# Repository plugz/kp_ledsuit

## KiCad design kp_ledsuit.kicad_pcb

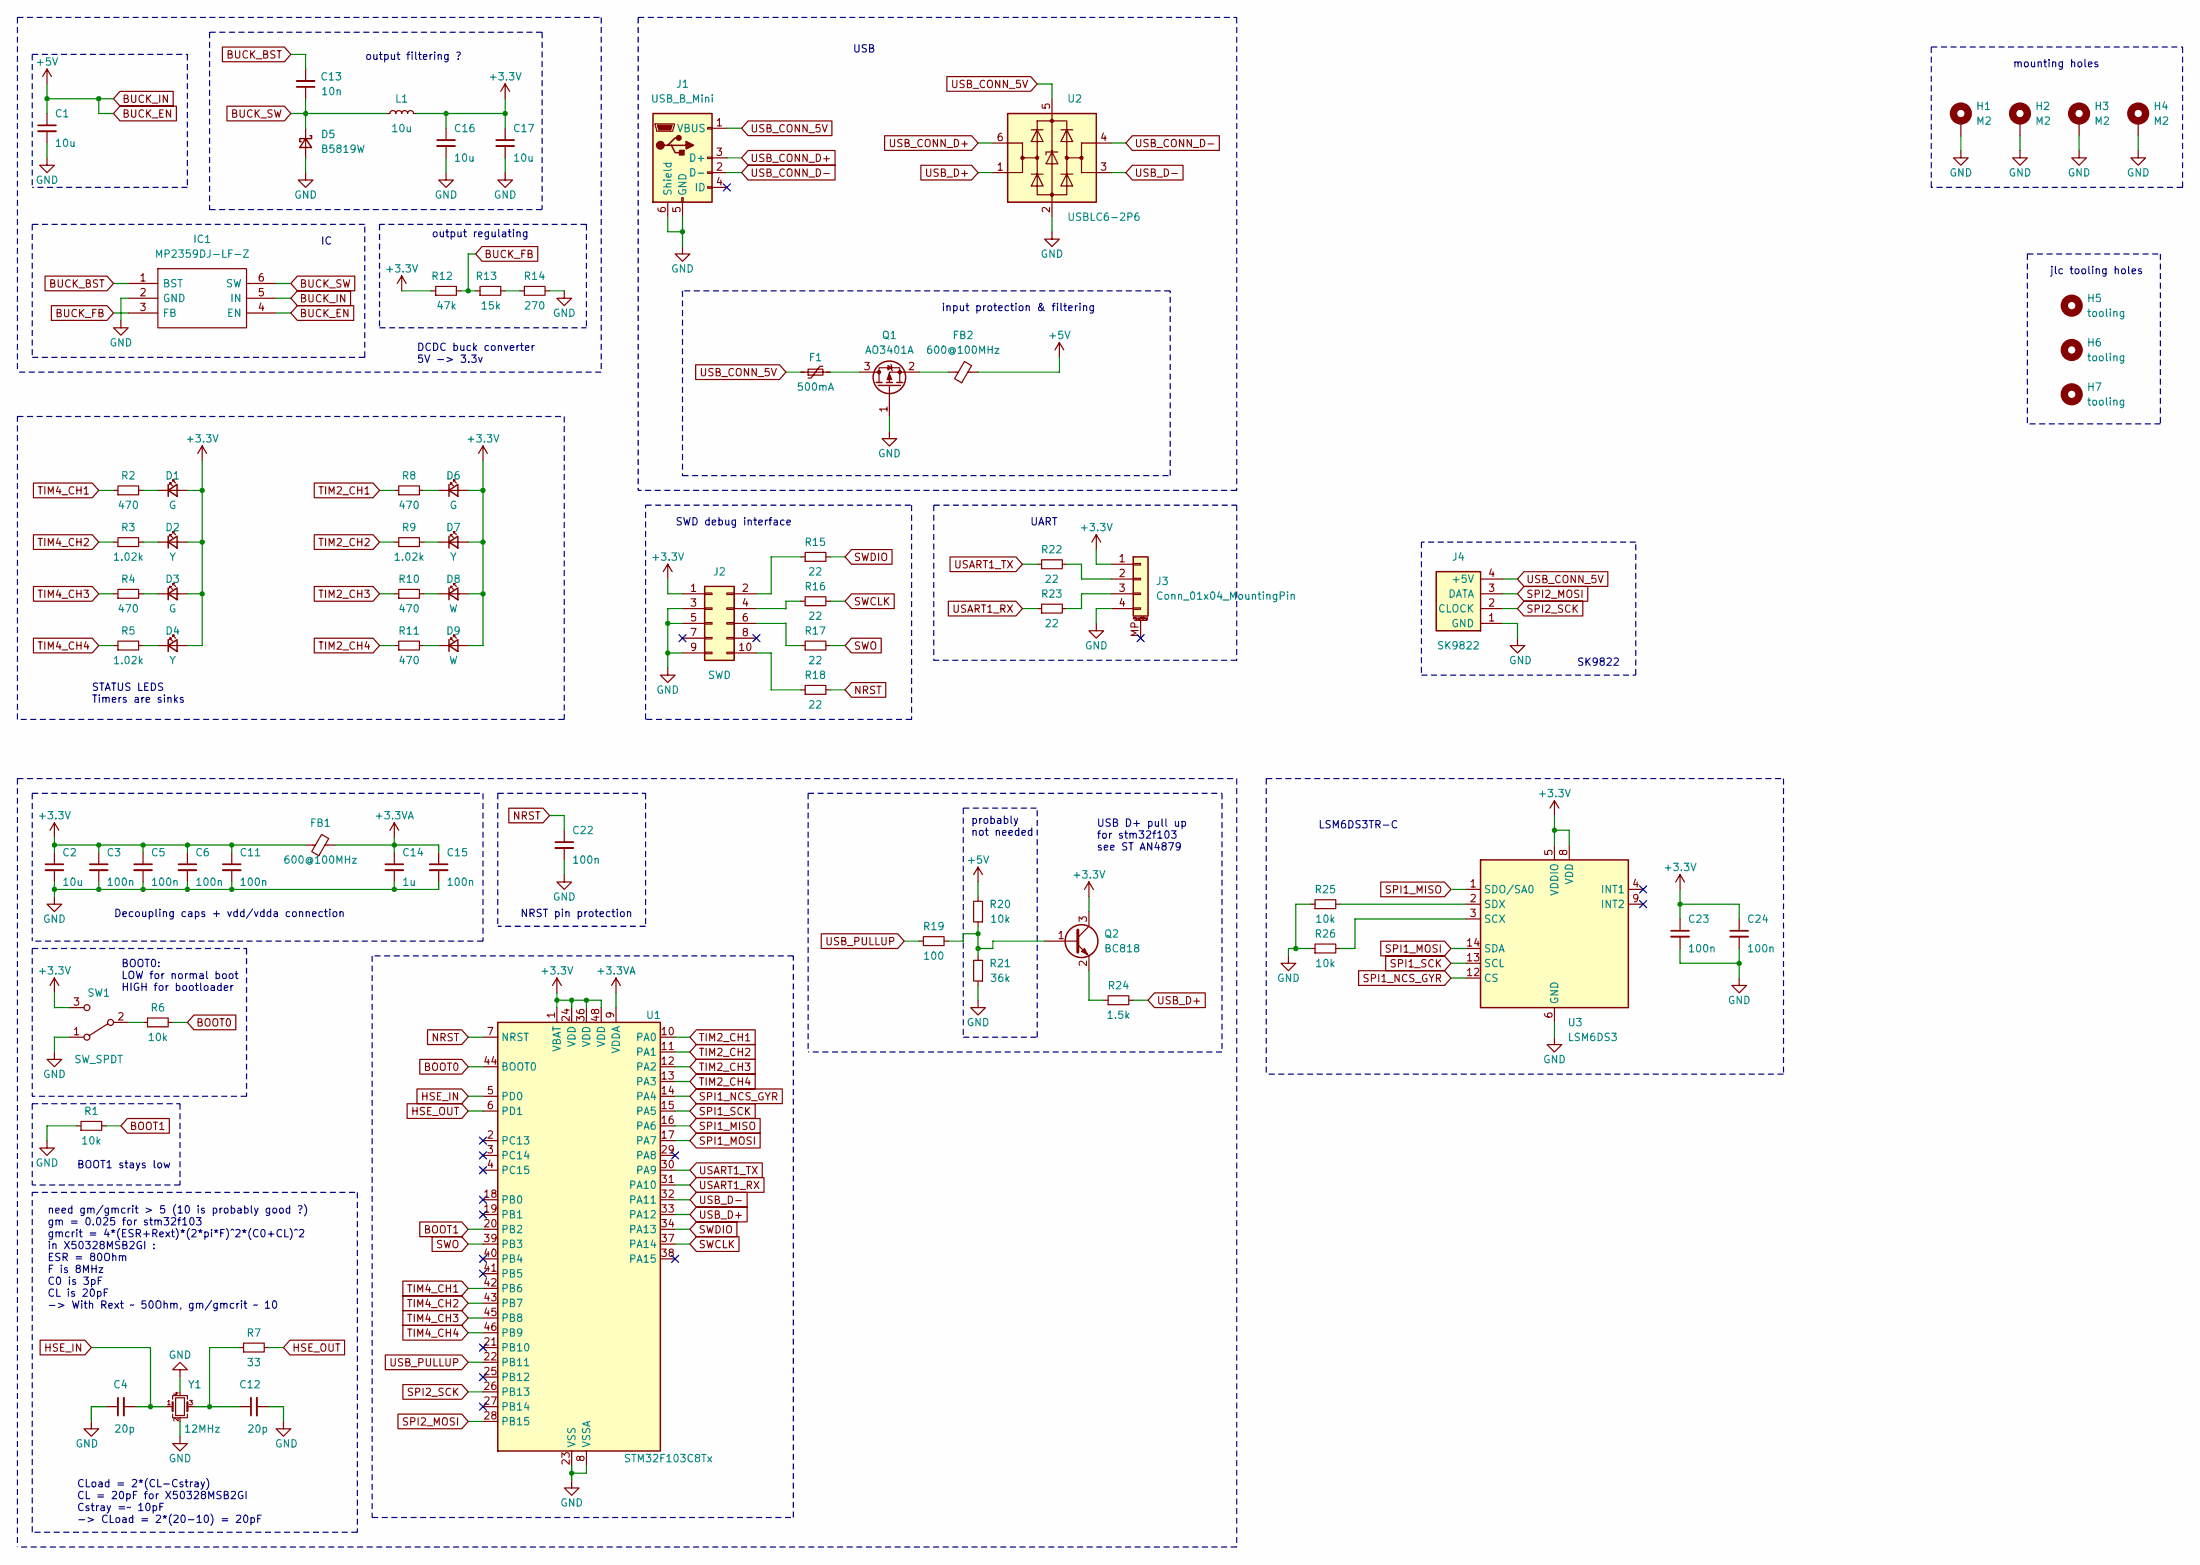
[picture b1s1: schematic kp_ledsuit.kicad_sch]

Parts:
C1, C2, C16, C17: 10u; C_1206_3216Metric; JLCPCB Part # C13585
C3, C5, C6, C11, C15, C22, C23, C24: 100n; C_0402_1005Metric; JLCPCB Part # C307331
C4, C12: 20p; C_0402_1005Metric; JLCPCB Part # C1554
C13: 10n; C_0603_1608Metric; JLCPCB Part # C57112
C14: 1u; C_0805_2012Metric; JLCPCB Part # C28323
D1, D3, D6: G; LED_0805_2012Metric; JLCPCB Part # C2297
D2, D4, D7: Y; LED_0805_2012Metric; JLCPCB Part # C2296
D5: B5819W; D_SOD-123; JLCPCB Part # C8598
D8, D9: W; LED_0805_2012Metric; JLCPCB Part # C34499
F1: 500mA; Fuse_1206_3216Metric; JLCPCB Part # C2984676
FB1, FB2: 600@100MHz; L_0805_2012Metric; JLCPCB Part # C1017
H1, H2, H3, H4: M2; MountingHole_2.2mm_M2_Pad_Via
H5, H6, H7: tooling; jlc_tooling_hole
IC1: MP2359DJ-LF-Z; SOT95P280X100-6N; Manufacturer_Part_Number MP2359DJ-LF-Z; Mouser Part Number 946-MP2359DJLFZ
J1: USB_B_Mini; USB_Mini-B_Wuerth_65100516121_Horizontal
J2: SWD; PinSocket_2x05_P1.27mm_Vertical_SMD
J3: Conn_01x04_MountingPin; Molex_PicoBlade_53261-0471_1x04-1MP_P1.25mm_Horizontal
J4: SK9822; SK9822_edge_solder
L1: 10u; L_Sunlord_MWSA0503S; JLCPCB Part # C408412
Q1: AO3401A; SOT-23; JLCPCB Part # C15127
Q2: BC818; SOT-23; JLCPCB Part # C154797
R1, R6, R25, R26: 10k; R_0603_1608Metric; JLCPCB Part # C25804
R2, R4, R8, R10, R11: 470; R_0805_2012Metric; JLCPCB Part # C17710
R3, R5, R9: 1.02k; R_0805_2012Metric; JLCPCB Part # C17369
R7: 33; R_0402_1005Metric; JLCPCB Part # C25105
R12: 47k; R_1206_3216Metric
R13: 15k; R_1206_3216Metric
R14: 270; R_1206_3216Metric
R15, R16, R17, R18, R22, R23: 22; R_0402_1005Metric; JLCPCB Part # C25092
R19: 100; R_0603_1608Metric; JLCPCB Part # C22775
R20: 10k; R_0603_1608Metric
R21: 36k; R_0603_1608Metric
R24: 1.5k; R_0603_1608Metric; JLCPCB Part # C22843
SW1: SW_SPDT; SW_SPDT_PCM12
U1: STM32F103C8Tx; LQFP-48_7x7mm_P0.5mm; JLCPCB Part # C8734
U2: USBLC6-2P6; SOT-666; JLCPCB Part # C15999
U3: LSM6DS3; LGA-14_3x2.5mm_P0.5mm_LayoutBorder3x4y; JLCPCB Part # C967633
Y1: 12MHz; Crystal_SMD_3225-4Pin_3.2x2.5mm; JLCPCB Part # C9002

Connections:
+3.3V: C2.1, C3.1, C5.1, C6.1, C11.1, C16.1, C17.1, C23.1, C24.1, D1.2 (A), D2.2 (A), D3.2 (A), D4.2 (A), D6.2 (A), D7.2 (A), D8.2 (A), D9.2 (A), FB1.1, J2.1, J3.1, L1.2, Q2.3 (C), R12.1, SW1.3 (C), U1.1 (VBAT), U1.24 (VDD), U1.36 (VDD), U1.48 (VDD), U3.5 (VDDIO), U3.8 (VDD)
+3.3VA: C14.1, C15.1, FB1.2, U1.9 (VDDA)
BOOT0: R6.2, U1.44 (BOOT0)
BOOT1: R1.2, U1.20 (PB2)
BUCK_BST: C13.2, IC1.1 (BST)
BUCK_EN: C1.1, FB2.2, IC1.4 (EN), IC1.5 (IN), R20.2
BUCK_FB: IC1.3 (FB), R12.2, R13.1
BUCK_SW: C13.1, D5.1 (K), IC1.6 (SW), L1.1
GND: C1.2, C2.2, C3.2, C4.1, C5.2, C6.2, C11.2, C12.2, C14.2, C15.2, C16.2, C17.2, C22.2, C23.2, C24.2, D5.2 (A), H1.1, H2.1, H3.1, H4.1, IC1.2 (GND), J1.5 (GND), J1.6 (Shield), J2.3, J2.5, J2.9, J3.4, J4.1 (GND), Q1.1 (G), R1.1, R14.2, R21.1, R25.1, R26.1, SW1.1 (A), U1.8 (VSSA), U1.23 (VSS), U1.35 (VSS), U1.47 (VSS), U2.2 (GND), U3.6 (GND), U3.7 (GND), Y1.2, Y1.4
HSE_IN: C4.2, U1.5 (PD0), Y1.1
HSE_OUT: R7.2, U1.6 (PD1)
NRST: C22.1, R18.2, U1.7 (NRST)
unnamed: C12.1, R7.1, Y1.3
unnamed: D1.1 (K), R2.2
unnamed: D2.1 (K), R3.2
unnamed: D3.1 (K), R4.2
unnamed: D4.1 (K), R5.2
unnamed: D6.1 (K), R8.2
unnamed: D7.1 (K), R9.2
unnamed: D8.1 (K), R10.2
unnamed: D9.1 (K), R11.2
unnamed: J2.2, R15.1
unnamed: J2.4, R16.1
unnamed: J2.6, R17.1
unnamed: J2.10, R18.1
unnamed: J3.2, R22.2
unnamed: J3.3, R23.2
unnamed: F1.2, Q1.3 (D)
unnamed: FB2.1, Q1.2 (S)
unnamed: Q2.1 (B), R19.2, R20.1, R21.2
unnamed: Q2.2 (E), R24.1
unnamed: R13.2, R14.1
unnamed: R6.1, SW1.2 (B)
unnamed: R26.2, U3.3 (SCX)
unnamed: R25.2, U3.2 (SDX)
SPI1_MISO: U1.16 (PA6), U3.1 (SDO/SA0)
SPI1_MOSI: U1.17 (PA7), U3.14 (SDA)
SPI1_NCS_GYR: U1.14 (PA4), U3.12 (CS)
SPI1_SCK: U1.15 (PA5), U3.13 (SCL)
SPI2_MOSI: J4.3 (DATA), U1.28 (PB15)
SPI2_SCK: J4.2 (CLOCK), U1.26 (PB13)
SWCLK: R16.2, U1.37 (PA14)
SWDIO: R15.2, U1.34 (PA13)
SWO: R17.2, U1.39 (PB3)
TIM2_CH1: R8.1, U1.10 (PA0)
TIM2_CH2: R9.1, U1.11 (PA1)
TIM2_CH3: R10.1, U1.12 (PA2)
TIM2_CH4: R11.1, U1.13 (PA3)
TIM4_CH1: R2.1, U1.42 (PB6)
TIM4_CH2: R3.1, U1.43 (PB7)
TIM4_CH3: R4.1, U1.45 (PB8)
TIM4_CH4: R5.1, U1.46 (PB9)
USART1_RX: R23.1, U1.31 (PA10)
USART1_TX: R22.1, U1.30 (PA9)
USB_CONN_5V: F1.1, J1.1 (VBUS), J4.4 (+5V), U2.5 (VBUS)
USB_CONN_D+: J1.3 (D+), U2.6 (I/O1)
USB_CONN_D-: J1.2 (D-), U2.4 (I/O2)
USB_D+: R24.2, U1.33 (PA12), U2.1 (I/O1)
USB_D-: U1.32 (PA11), U2.3 (I/O2)
USB_PULLUP: R19.1, U1.22 (PB11)

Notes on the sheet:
USB
UART
output filtering ?
LSM6DS3TR-C
USB D+ pull up for stm32f103 see ST AN4879
STATUS LEDS Timers are sinks
DCDC buck converter 5V -> 3.3v
input protection & filtering
BOOT1 stays low
jlc tooling holes
output regulating
need gm/gmcrit > 5 (10 is probably good ?) gm = 0.025 for stm32f103 gmcrit = 4*(ESR+Rext)*(2*pi*F)^2*(C0+CL)^2 in X50328MSB2GI : ESR = 80Ohm F is 8MHz C0 is 3pF CL is 20pF -> With Rext ~ 50Ohm, gm/gmcrit ~ 10
CLoad = 2*(CL-Cstray) CL = 20pF for X50328MSB2GI Cstray =~ 10pF -> CLoad = 2*(20-10) = 20pF
NRST pin protection
Decoupling caps + vdd/vdda connection
SK9822
probably not needed
BOOT0: LOW for normal boot HIGH for bootloader
SWD debug interface
mounting holes

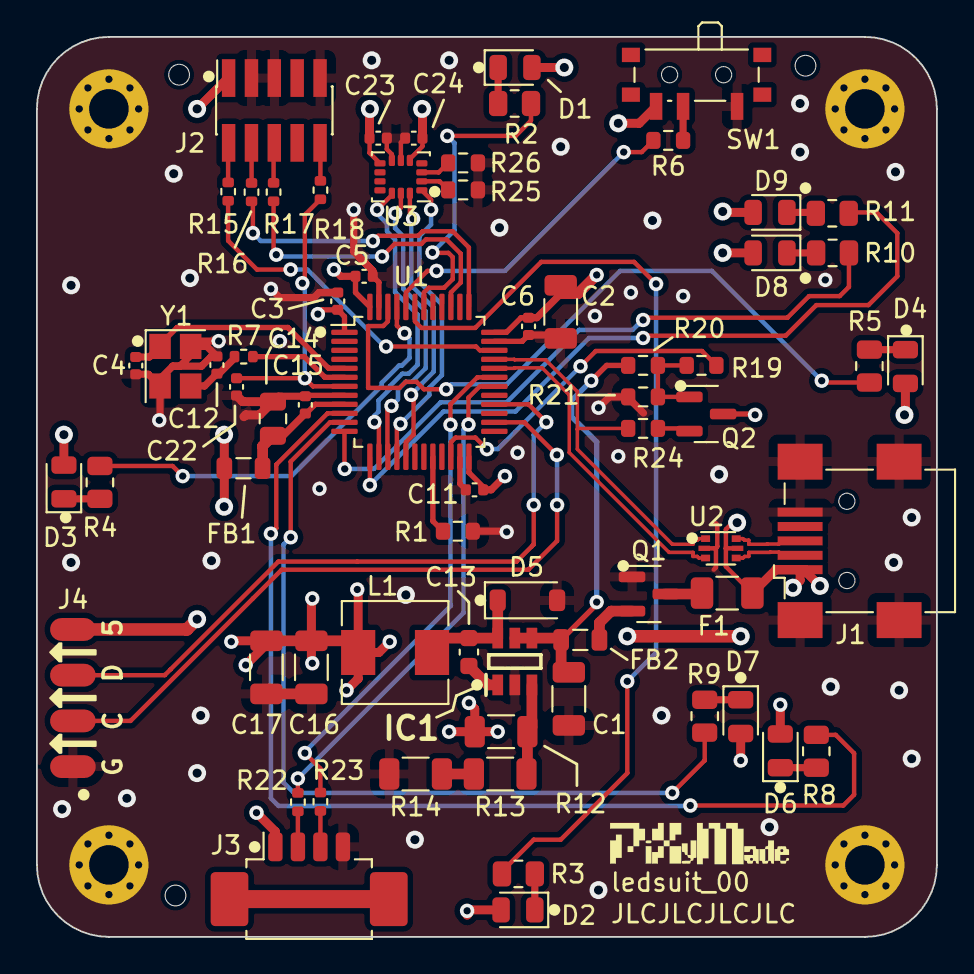
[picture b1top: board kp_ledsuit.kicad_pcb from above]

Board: 4 copper layers, 50.0 x 50.0 mm, 74 parts (0 on the bottom side), 60 nets.

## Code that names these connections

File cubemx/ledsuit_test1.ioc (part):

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Mcu.Name=STM32F103C(8-B)Tx
Mcu.Package=LQFP48
Mcu.UserName=STM32F103C8Tx
PA0-WKUP.Signal=S_TIM2_CH1_ETR
PA1.Signal=S_TIM2_CH2
PA10.Mode=Asynchronous
PA10.Signal=USART1_RX
PA11.Mode=Device
PA11.Signal=USB_DM
PA12.Mode=Device
PA12.Signal=USB_DP
PA13.Mode=Trace_Asynchronous_SW
PA13.Signal=SYS_JTMS-SWDIO
PA14.Mode=Trace_Asynchronous_SW
PA14.Signal=SYS_JTCK-SWCLK
PA2.Signal=S_TIM2_CH3
PA3.Signal=S_TIM2_CH4
PA4.GPIOParameters=GPIO_Label
PA4.GPIO_Label=SPI1_NCS_GYR
PA4.Signal=GPIO_Output
PA5.Mode=Full_Duplex_Master
PA5.Signal=SPI1_SCK
PA6.Mode=Full_Duplex_Master
PA6.Signal=SPI1_MISO
PA7.Mode=Full_Duplex_Master
PA7.Signal=SPI1_MOSI
PA9.Mode=Asynchronous
PA9.Signal=USART1_TX
PB11.GPIOParameters=GPIO_Label
PB11.GPIO_Label=USB_PULLUP
PB11.Signal=GPIO_Output
PB13.Mode=TX_Only_Simplex_Unidirect_Master
PB13.Signal=SPI2_SCK
PB15.Mode=TX_Only_Simplex_Unidirect_Master
PB15.Signal=SPI2_MOSI
PB3.Mode=Trace_Asynchronous_SW
PB3.Signal=SYS_JTDO-TRACESWO
PB6.Signal=S_TIM4_CH1
PB7.Signal=S_TIM4_CH2
PB8.Signal=S_TIM4_CH3
PB9.Signal=S_TIM4_CH4
PD0-OSC_IN.Mode=HSE-External-Oscillator
PD0-OSC_IN.Signal=RCC_OSC_IN
PD1-OSC_OUT.Mode=HSE-External-Oscillator
PD1-OSC_OUT.Signal=RCC_OSC_OUT
RCC.HSE_VALUE=12000000
RCC.SYSCLKFreq_VALUE=72000000
RCC.SYSCLKSource=RCC_SYSCLKSOURCE_PLLCLK
board=custom

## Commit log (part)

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2024-02-05 add empty kicad project
2024-02-22 add stm32
2024-02-22 add power, usb, swd, onboard leds
2024-02-24 add IMU & SKconn + move input protections to USB part
2024-02-24 add test logo
2024-02-24 begin layout
2024-02-26 WIP first proto layout: 1 face
2024-02-26 pxm test logo
2024-03-02 v00 - send to prod
2026-02-15 update to kicad9
